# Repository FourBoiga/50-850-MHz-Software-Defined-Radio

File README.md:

# Wideband SDR (50–850 MHz)

## Overview

This project is a custom software-defined radio (SDR) designed to receive signals from approximately **50 MHz to 850 MHz**. The goal is to build a modular, low-cost SDR while learning RF engineering, analog design, FPGA development, and digital signal processing from the ground up.

Unlike many hobby SDRs that rely heavily on highly integrated tuner/transceiver ICs, this design uses discrete RF building blocks for much of the signal chain, including filtering, switching, amplification, mixing, local oscillator generation, and quadrature I/Q conversion.

---

## Goals

* Receive signals from approximately 50 MHz to 850 MHz
* Modular RF front-end
* Good dynamic range
* Low noise figure
* Quadrature I/Q output
* FPGA-based digital signal processing
* USB interface to a host PC
* Eventually interface with SDR software such as SDR++
* Learn professional RF and DSP design techniques

---

## Current Architecture

The signal starts at the antenna and passes through the RF protection and switched bandpass filter bank before being amplified by the LNA. From there it goes through the quadrature receiver and intermediate-frequency conversion stages, producing differential I/Q signals for the ADC. The ADC sends the digitized samples to the FPGA, where the DSP will be performed before the data is eventually sent to the host PC over USB.

---

The receiver uses multiple local oscillator paths generated from PLL frequency synthesizers referenced to a stable TCXO.

---

## Specifications

| Parameter           |                    Specification |
| ------------------- | -------------------------------: |
| Frequency Range     |                      ~50–850 MHz |
| Architecture        | Superheterodyne / Quadrature I/Q |
| Target IF Bandwidth |                           ~1 MHz |
| ADC                 |                       LTC2323-12 |
| ADC Resolution      |                           12-bit |
| ADC Sample Rate     |                   5 MSPS/channel |
| ADC Interface       |                              SPI |
| FPGA                |             Sipeed Tang Nano 20K |
| Controller          |                     STM32 Nucleo |
| Host Interface      |                              USB |
| Output              |              Digital I/Q samples |

These are design targets and specifications; final RF performance will be determined through hardware testing and characterization.

---

## RF Front End

The RF front end consists of:

* RF input protection
* Switched bandpass filter bank
* RF switching
* Low-noise amplifier
* Quadrature receiver/mixer
* Intermediate-frequency conversion
* Local oscillator generation
* PLL frequency synthesizers
* TCXO reference

### Filter Architecture

The original design included additional filtering after the LNA. After reviewing the local RF environment and considering the additional simulation and design time required, the post-LNA filters were removed from the architecture.

The remaining pre-LNA filter bank provides the primary out-of-band filtering before amplification.

---

## Local Oscillator

The local oscillator system uses:

* Stable TCXO reference
* PLL frequency synthesizers
* LO generation for the receiver mixer
* LO generation for the IF mixer

The LO circuitry and synthesizers have been fully integrated into the PCB design.

---

## I/Q Receiver

The receiver produces differential I/Q signals which are digitized by the LTC2323-12 ADC.

During PCB design, the polarity of the Q differential pair was found to be opposite to the polarity expected by the ADC. Rather than rerouting the completed RF section, the differential inputs are intentionally swapped.

This produces a 180° phase inversion of the Q component, which will be corrected digitally in the FPGA by negating the Q samples.

---

## ADC

The SDR uses an **LTC2323-12** dual-channel 12-bit SAR ADC.

The planned configuration uses:

* 12-bit resolution
* 5 MSPS per channel
* Differential I/Q inputs
* SPI interface
* Up to 105 MHz SPI clock

The ADC provides the interface between the analog I/Q receiver and the FPGA's digital signal-processing chain.

---

## FPGA and DSP

The next major development phase is the FPGA firmware and digital signal processing.

The FPGA will initially implement a minimal processing chain capable of receiving and processing the raw I/Q samples from the ADC.

Planned processing includes:

```text
ADC I/Q Samples
       │
       ▼
Digital Filtering
       │
       ▼
Frequency Translation
       │
       ▼
Decimation
       │
       ▼
Sample Formatting
       │
       ▼
USB / Host PC
```

The FPGA development will be done using the **Sipeed Tang Nano 20K**.

The initial goal is not to immediately implement complete SDR++ compatibility. The first fallback target is simply to get raw or minimally processed I/Q samples from the FPGA to a computer.

A simple Python-based host program can then perform FFT processing and display the received spectrum. This provides a straightforward way to verify the complete RF → ADC → FPGA → PC signal path before implementing a more complete SDR software interface.

---

## PCB

The PCB design is now complete and is undergoing a final review before manufacturing.

Completed PCB work includes:

* RF protection
* Bandpass filter bank
* RF switching
* LNA
* Receiver/mixer circuitry
* Local oscillator circuitry
* PLL synthesizers
* I/Q differential routing
* ADC interface
* FPGA interface
* STM32 controller interface
* USB-C circuitry
* Debug SMA connector
* 50 Ω test line
* Test points
* Debug interfaces

The next steps are to perform the final PCB review, finalize the BOM, and submit the project for manufacturing/funding.

---

## Software

### FPGA

Planned FPGA functionality includes:

* LTC2323-12 SPI interface
* I/Q sample capture
* Q polarity correction
* Digital filtering
* Digital frequency translation
* Decimation
* I/Q data formatting
* USB data streaming

### Host PC

The initial host software will likely be a simple Python-based development tool capable of:

* Receiving I/Q samples
* Converting ADC samples into complex I/Q data
* Performing FFTs
* Displaying frequency spectra
* Visualizing received signals

The long-term goal is compatibility with existing SDR software such as SDR++.

---

## Major Engineering Challenges

* Wideband RF filter design
* RF PCB layout
* Maintaining controlled RF impedance
* Mixer integration
* Local oscillator synthesis
* LO phase noise
* Dynamic range
* Noise figure
* I/Q signal integrity
* ADC interfacing
* High-speed SPI
* FPGA DSP implementation
* Fixed-point digital signal processing
* Host-side I/Q streaming
* SDR software integration

One of the primary goals of the project is to understand and implement these individual systems rather than relying on a highly integrated SDR transceiver to hide their operation.

---

## Long-Term Goals

This project is intended to serve as a platform for experimentation and learning in:

* RF Engineering
* Analog Electronics
* RF PCB Design
* FPGA Development
* Digital Signal Processing
* Software-Defined Radio
* Communication Systems

Future revisions may improve filtering, dynamic range, instantaneous bandwidth, frequency coverage, DSP capabilities, and host software.

---

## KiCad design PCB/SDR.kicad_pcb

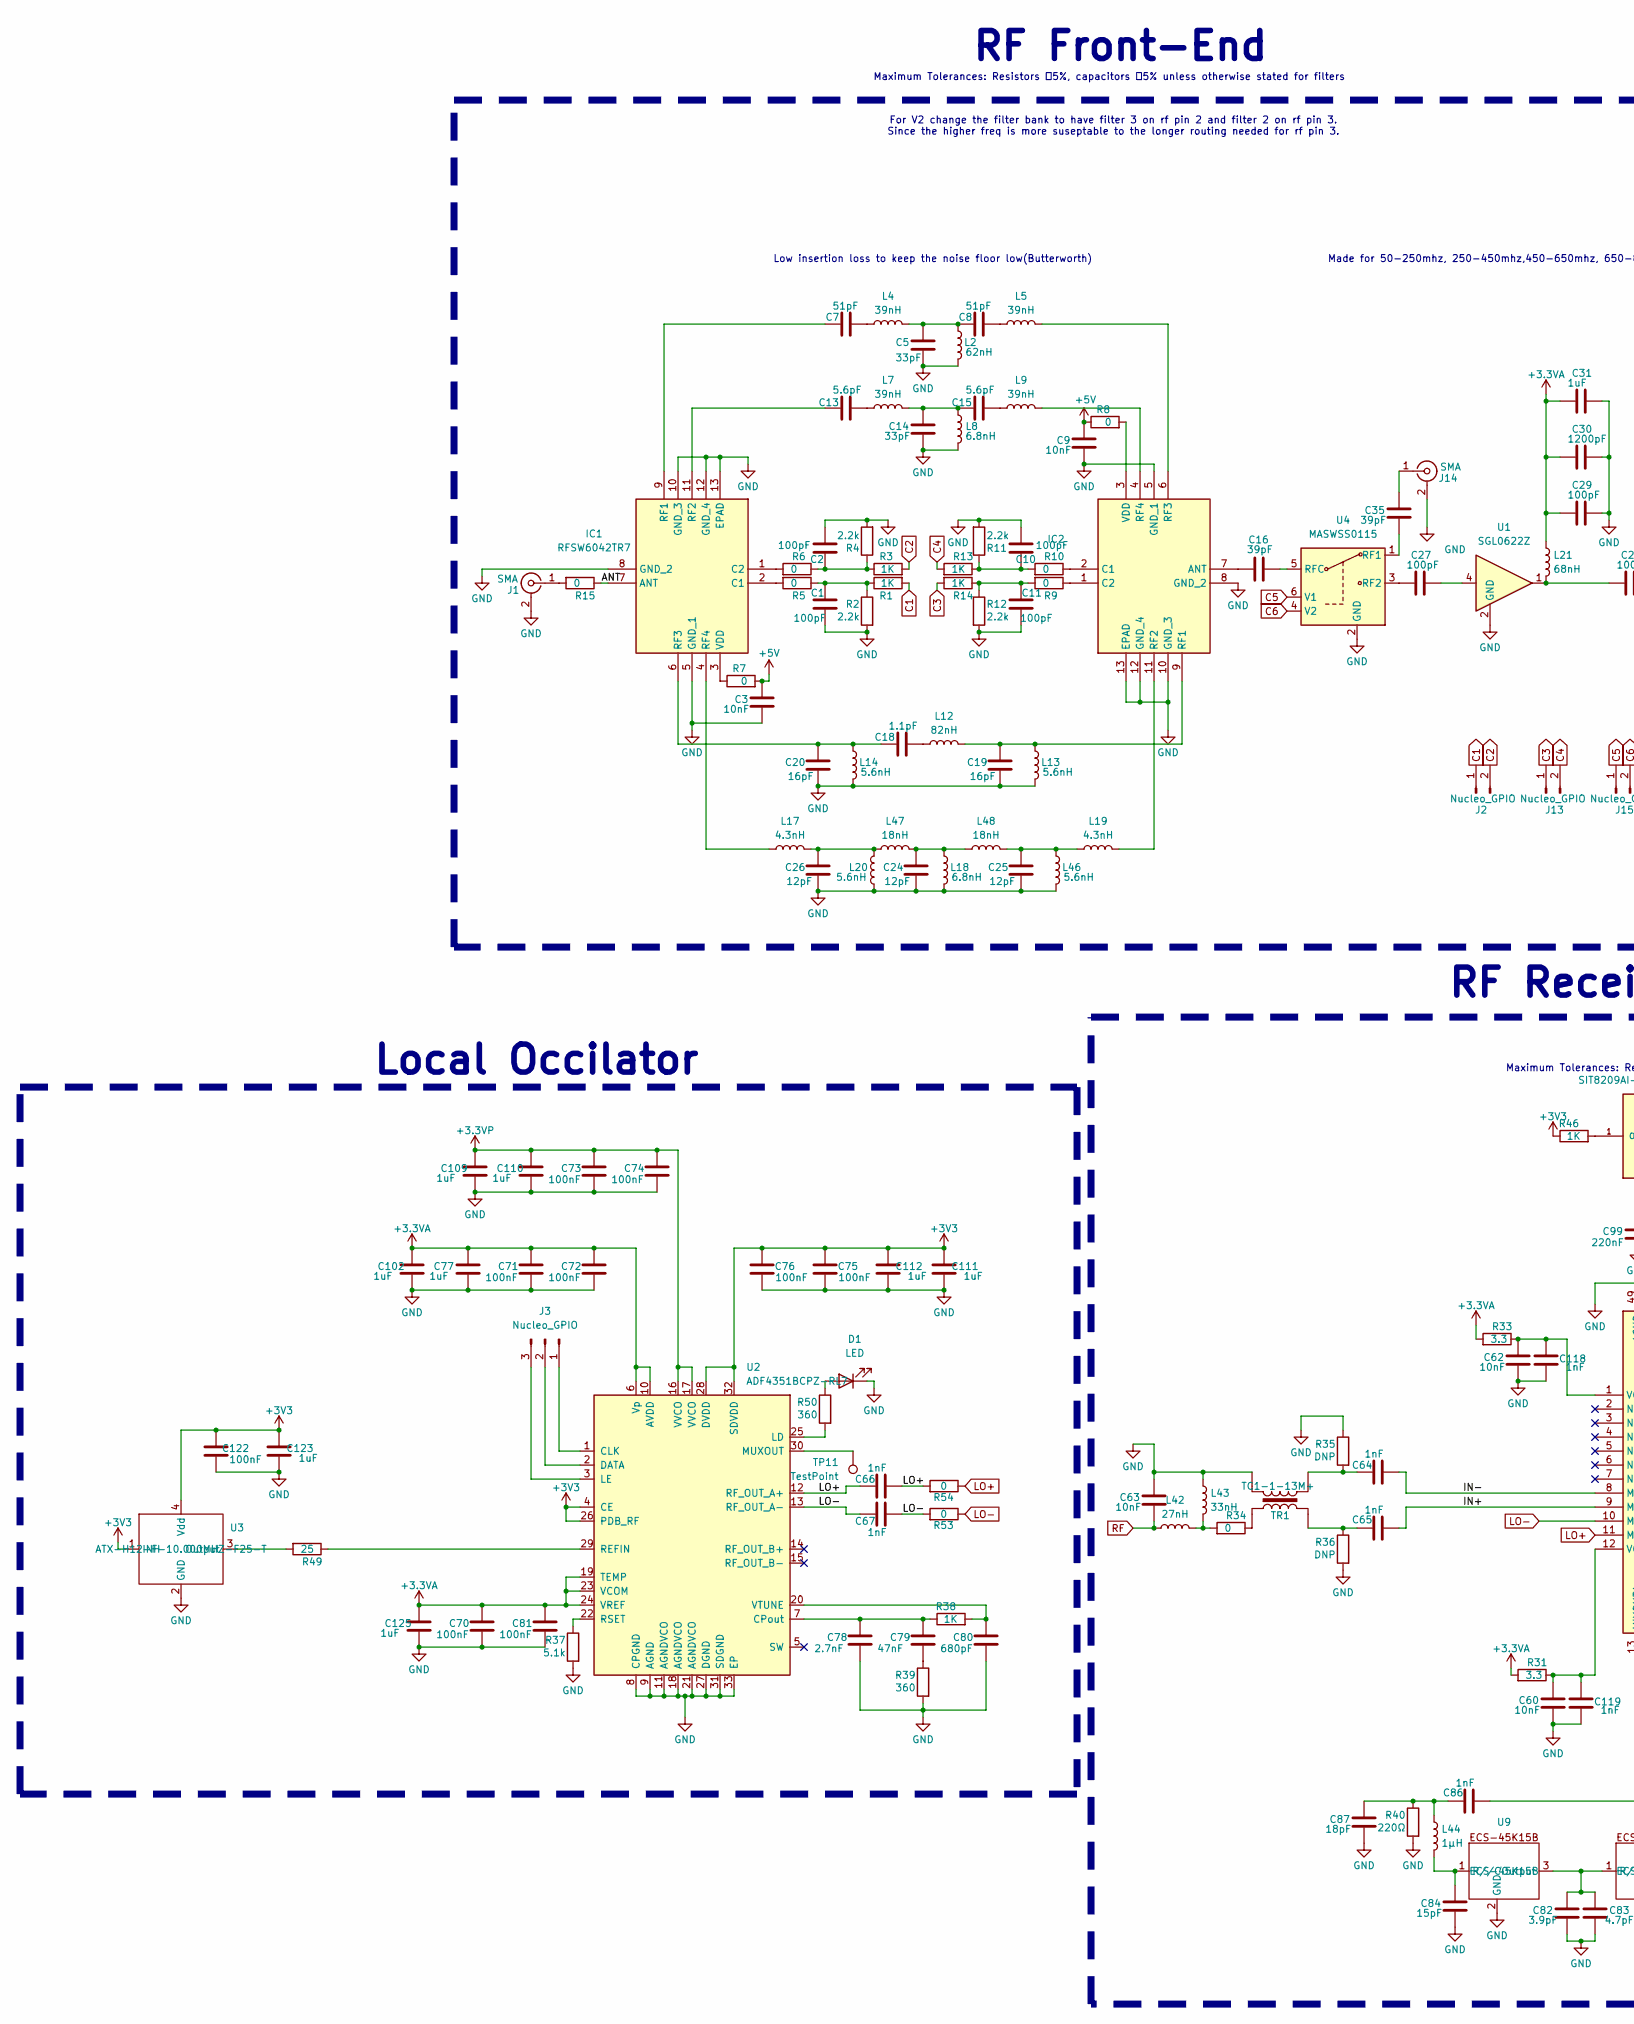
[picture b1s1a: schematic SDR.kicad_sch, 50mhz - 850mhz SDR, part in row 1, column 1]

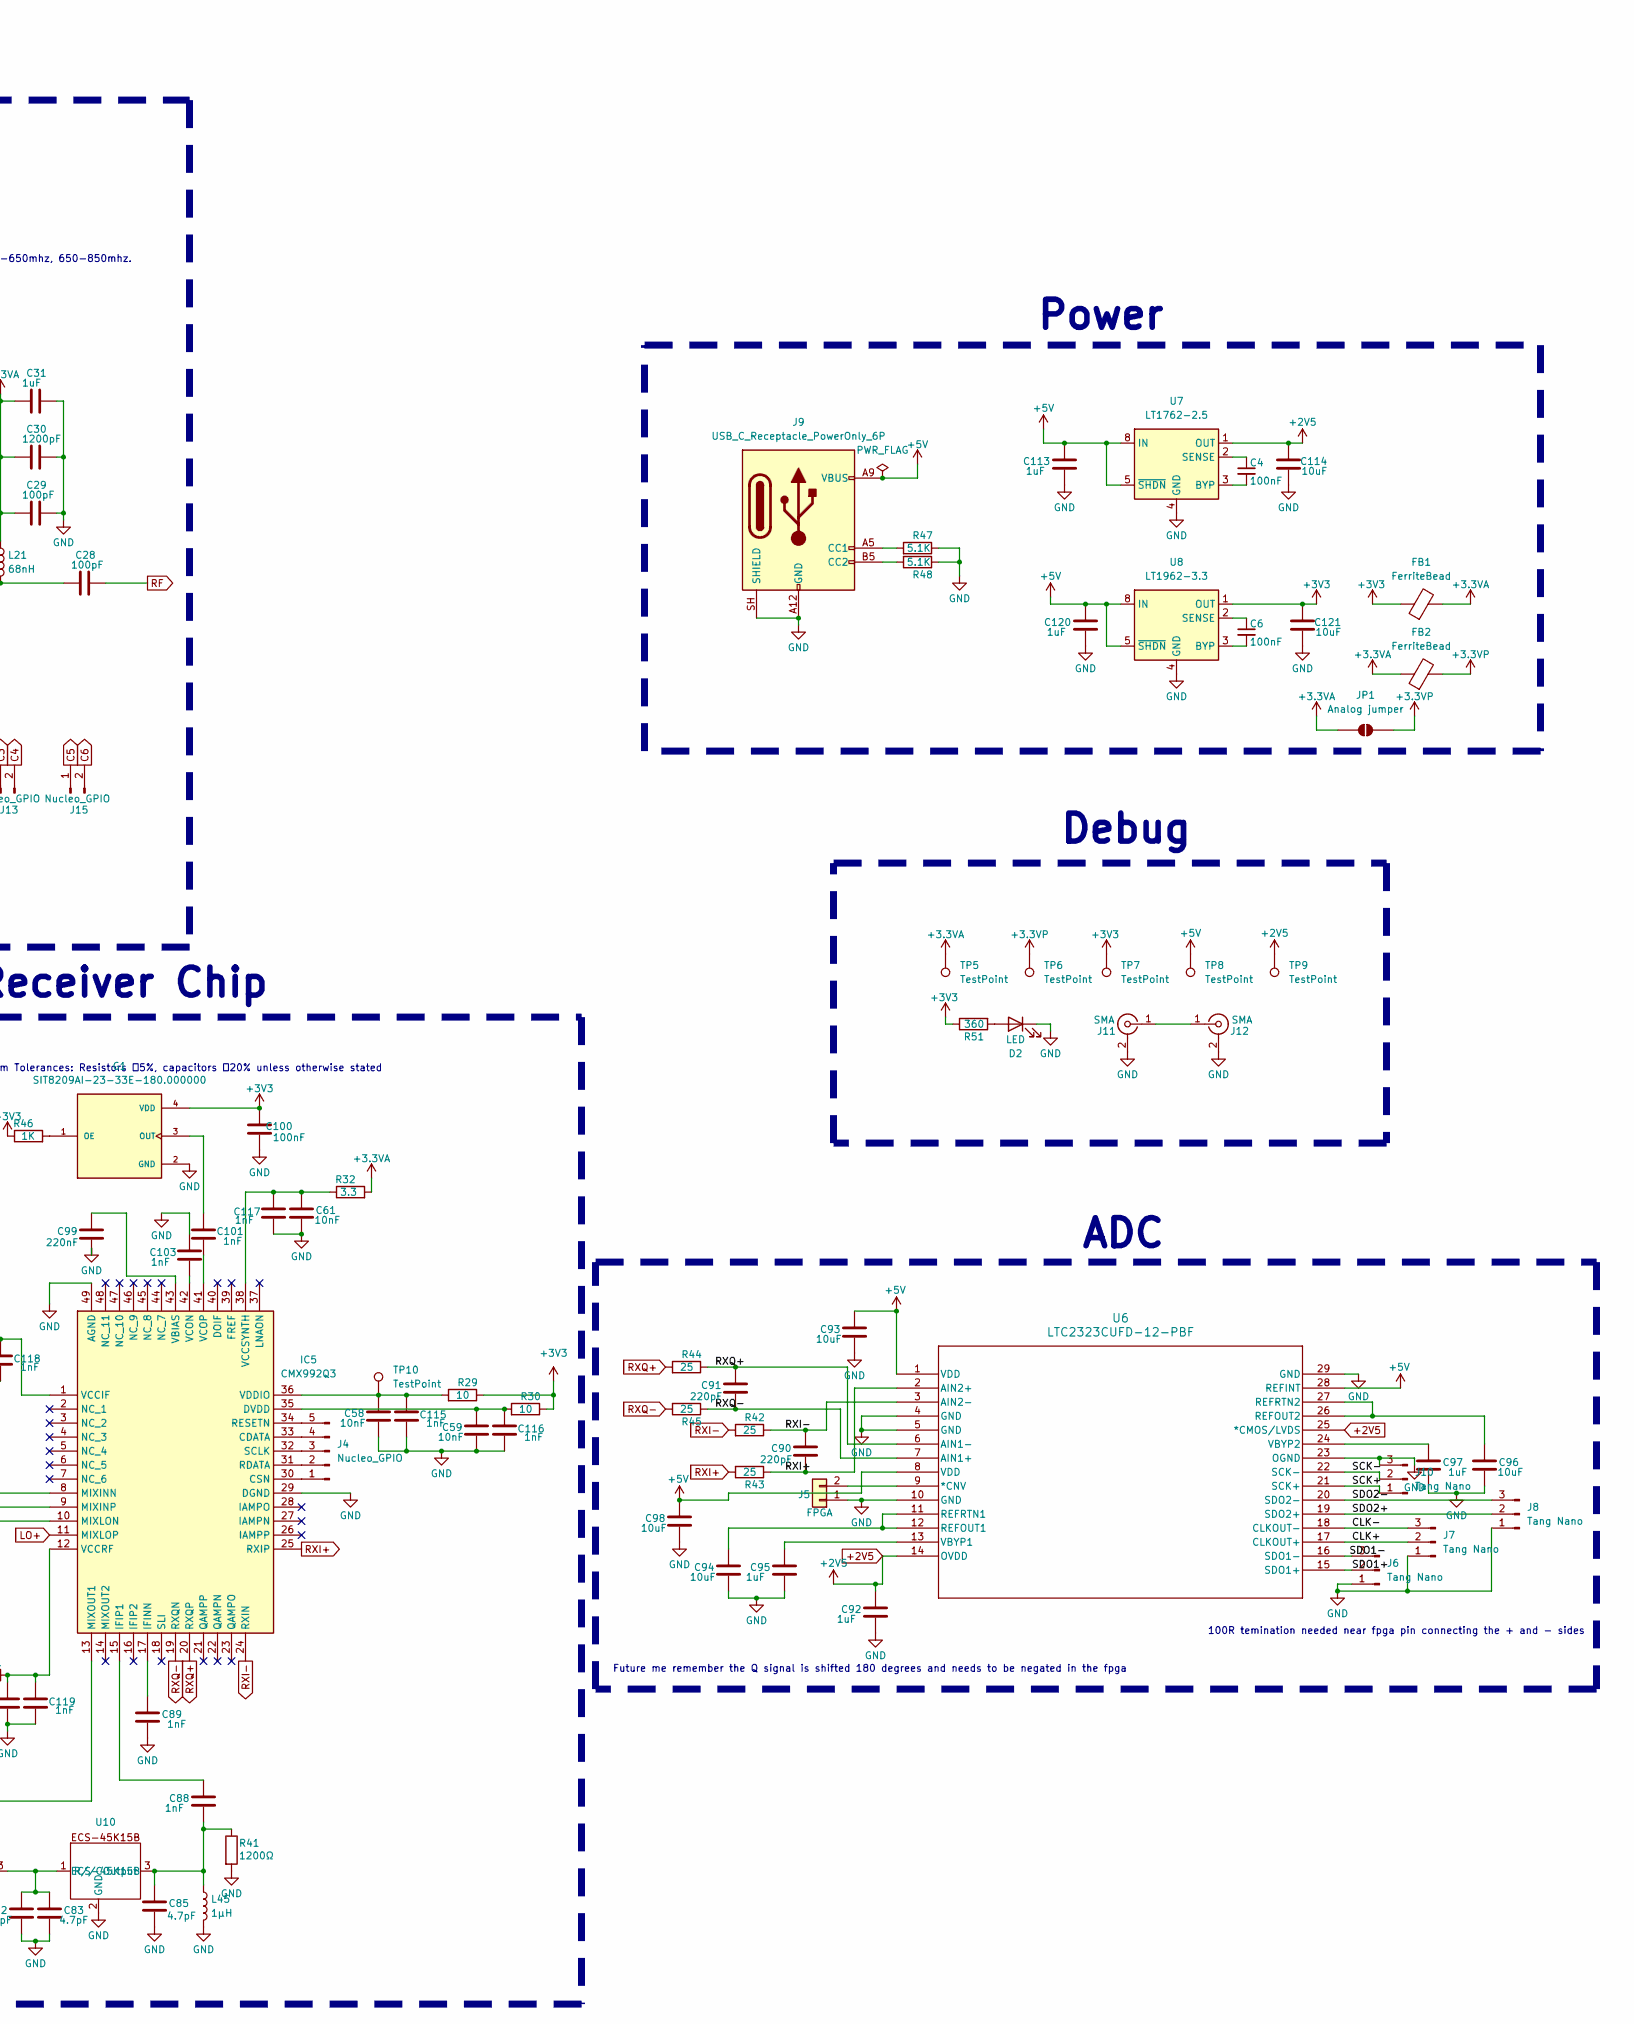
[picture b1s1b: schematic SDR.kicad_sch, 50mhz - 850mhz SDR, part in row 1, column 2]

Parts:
C1, C2, C10, C11, C27, C28, C29: 100pF; C_0402_1005Metric
C3, C9, C58, C59, C60, C61, C62, C63: 10nF; C_0805_2012Metric
C4, C6, C70, C73, C74, C75, C76, C81, C100: 100nF; C_0603_1608Metric
C5, C14: 33pF; C_0402_1005Metric
C7, C8: 51pF; C_0402_1005Metric
C13, C15: 5.6pF; C_0402_1005Metric
C16, C35: 39pF; C_0402_1005Metric
C18: 1.1pF; C_0402_1005Metric
C19, C20: 16pF; C_0402_1005Metric
C24, C25, C26: 12pF; C_0402_1005Metric
C30: 1200pF; C_0402_1005Metric
C31, C77, C92, C95, C97, C102, C109, C110, C111, C112, C113, C120, C123, C125: 1uF; C_0603_1608Metric
C64, C65, C66, C67, C86, C88, C89, C101, C103, C115, C116, C117, C118, C119: 1nF; C_0603_1608Metric
C71, C72, C122: 100nF; C_0402_1005Metric
C78: 2.7nF; C_0603_1608Metric
C79: 47nF; C_0603_1608Metric
C80: 680pF; C_0603_1608Metric
C82: 3.9pF; C_0603_1608Metric
C83, C85: 4.7pF; C_0603_1608Metric
C84: 15pF; C_0603_1608Metric
C87: 18pF; C_0603_1608Metric
C90, C91: 220pF; C_0603_1608Metric
C93, C94, C96, C98: 10uF; C_0805_2012Metric
C99: 220nF; C_0603_1608Metric
C114, C121: 10uF; C_0603_1608Metric
D1, D2: LED; LED_0603_1608Metric
FB1, FB2: FerriteBead; L_0603_1608Metric
G1: SIT8209AI-23-33E-180.000000; OSC_SiT8209AI-32-25E-133.300000; PARTREV 1.1
IC1, IC2: RFSW6042TR7; QFN40P180X180X60-13N-D; Mouser Part Number 772-RFSW6042
IC5: CMX992Q3; QFN50P700X700X100-49N-D; Mouser Part Number 226-CMX992Q3
J1, J11, J12: SMA; SMA_Amphenol_132289_EdgeMount
J2, J13, J15: Nucleo_GPIO; PinHeader_1x02_P1.00mm_Vertical
J3: Nucleo_GPIO; PinHeader_1x03_P1.00mm_Vertical
J4: Nucleo_GPIO; PinHeader_1x05_P1.00mm_Vertical
J5: FPGA; SolderWire-0.25sqmm_1x02_P4.2mm_D0.65mm_OD1.7mm
J6, J7, J8, J10: Tang Nano; SolderWire-0.25sqmm_1x03_P4.5mm_D0.65mm_OD2mm
J9: USB_C_Receptacle_PowerOnly_6P; USB_C_Receptacle_GCT_USB4125-xx-x-0190_6P_TopMnt_Horizontal
J14: SMA; SMA_Amphenol_132291-12_Vertical
JP1: Analog jumper; SolderJumper-2_P1.3mm_Open_Pad1.0x1.5mm
L2: 62nH; L_0603_1608Metric
L4, L5, L7, L9: 39nH; L_0603_1608Metric
L8, L18: 6.8nH; L_0603_1608Metric
L12: 82nH; L_0805_2012Metric
L13, L14, L20, L46: 5.6nH; L_0402_1005Metric
L17, L19: 4.3nH; L_0402_1005Metric
L21: 68nH; L_0603_1608Metric
L42: 27nH; L_0603_1608Metric
L43: 33nH; L_0603_1608Metric
L44, L45: 1μH; L_0805_2012Metric
L47, L48: 18nH; L_0603_1608Metric
R1, R3, R13, R14, R38, R46: 1K; R_0402_1005Metric
R2, R4, R11, R12: 2.2k; R_0402_1005Metric
R5, R6, R7, R8, R9, R10, R15: 0; R_0402_1005Metric
R29, R30: 10; R_0402_1005Metric
R31, R32, R33: 3.3; R_0603_1608Metric
R34, R53, R54: 0; R_0603_1608Metric
R35, R36: DNP; R_0603_1608Metric
R37: 5.1k; R_0402_1005Metric
R39, R51: 360; R_0603_1608Metric
R40: 220Ω; R_0603_1608Metric
R41: 1200Ω; R_0603_1608Metric
R42, R43, R44, R45, R49: 25; R_0805_2012Metric
R47, R48: 5.1K; R_0402_1005Metric
R50: 360; R_0402_1005Metric
TP5, TP6, TP7, TP8, TP9: TestPoint; TestPoint_Pad_D4.0mm
TP10, TP11: TestPoint; TestPoint_Pad_D2.0mm
TR1: TC1-1-13M+; AT224-1A
U1: SGL0622Z; DFN-8-1EP_2x2mm_P0.5mm_EP0.6x1.2mm
U2: ADF4351BCPZ-RL7; LFCSP-32-1EP_5x5mm_P0.5mm_EP3.25x3.25mm
U3: ATX-H12-F-10.000MHZ-F25-T; ATXH12F10000MHzF25T
U4: MASWSS0115; SOT-363_SC-70-6
U6: LTC2323CUFD-12-PBF; QFN-28_UFD_LIT
U7: LT1762-2.5; MSOP-8_3x3mm_P0.65mm
U8: LT1962-3.3; MSOP-8_3x3mm_P0.65mm
U9, U10: ECS-45K15B; Untitled

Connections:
+2V5: C92.1, C114.1, TP9.1 (1_1), U6.14 (OVDD), U6.25 (*CMOS/LVDS), U7.1 (OUT)
+3.3VA: C29.2, C30.2, C31.2, C70.1, C71.1, C72.1, C77.1, C81.1, C102.1, C125.1, FB1.2, FB2.1, JP1.1 (A), L21.1, R31.2, R32.2, R33.2, TP5.1 (1_1), U2.6 (Vp), U2.10 (AVDD), U2.19 (TEMP), U2.23 (VCOM), U2.24 (VREF)
+3.3VP: C73.1, C74.1, C109.1, C110.1, FB2.2, JP1.2 (B), TP6.1 (1_1), U2.16 (VVCO), U2.17 (VVCO)
+3V3: C75.1, C76.1, C100.1, C111.1, C112.1, C121.1, C122.1, C123.1, FB1.1, G1.4 (VDD), R29.1, R30.1, R46.1, R51.1, TP7.1 (1_1), U2.4 (CE), U2.26 (PDB_RF), U2.28 (DVDD), U2.32 (SDVDD), U3.1 (INH), U3.4 (Vdd), U8.1 (OUT)
+5V: C3.1, C9.1, C93.1, C98.1, C113.1, C120.1, J9.A9 (VBUS), J9.B9 (VBUS), R7.2, R8.1, TP8.1 (1_1), U6.1 (VDD), U6.8 (VDD), U6.28 (REFINT), U7.5 (~SHDN), U7.8 (IN), U8.5 (~SHDN), U8.8 (IN)
/ANT: IC1.7 (ANT), R15.1
/CLK+: J7.2, U6.17 (CLKOUT+)
/CLK-: J7.3, U6.18 (CLKOUT-)
/IN+: C65.1, IC5.9 (MIXINP)
/IN-: C64.1, IC5.8 (MIXINN)
/SCK+: J10.1, U6.21 (SCK+)
/SCK-: J10.2, U6.22 (SCK-)
/SDO1+: J6.2, U6.15 (SDO1+)
/SDO1-: J6.3, U6.16 (SDO1-)
/SDO2+: J8.2, U6.19 (SDO2+)
/SDO2-: J8.3, U6.20 (SDO2-)
C1: J2.1, R1.2
C2: J2.2, R3.2
C3: J13.1, R14.2
C4: J13.2, R13.2
C5: J15.1, U4.6 (V1)
C6: J15.2, U4.4 (V2)
GND: C1.2, C2.2, C3.2, C5.2, C9.2, C10.2, C11.2, C14.2, C19.2, C20.2, C24.2, C25.2, C26.2, C29.1, C30.1, C31.1, C58.2, C59.2, C60.2, C61.2, C62.2, C63.1, C70.2, C71.2, C72.2, C73.2, C74.2, C75.2, C76.2, C77.2, C78.2, C80.2, C81.2, C82.2, C83.2, C84.2, C85.2, C87.2, C89.2, C92.2, C93.2, C94.2, C95.2, C96.2, C97.2, C98.2, C99.2, C100.2, C102.2, C103.1, C109.2, C110.2, C111.2, C112.2, C113.2, C114.2, C115.2, C116.2, C117.2, C118.2, C119.2, C120.2, C121.2, C122.2, C123.2, C125.2, D1.1 (K), D2.1 (K), G1.2 (GND), IC1.5 (GND_1), IC1.8 (GND_2), IC1.10 (GND_3), IC1.12 (GND_4), IC1.13 (EPAD), IC2.5 (GND_1), IC2.8 (GND_2), IC2.10 (GND_3), IC2.12 (GND_4), IC2.13 (EPAD), IC5.29 (DGND), IC5.49 (AGND), J1.2 (Ext), J5.1, J6.1, J7.1, J8.1, J9.A12 (GND), J9.B12 (GND), J9.SH (SHIELD), J10.3, J11.2 (Ext), J12.2 (Ext), J14.2 (Ext), L2.2, L8.2, L13.2, L14.2, L18.2, L20.2, L43.1, L45.2, L46.2, R2.2, R4.2, R11.2, R12.2, R35.1, R36.2, R37.2, R39.2, R40.2, R41.2, R47.1, R48.1, TR1.6, U1.2 (GND), U1.3 (GND), U1.5 (GND), U1.6 (GND), U1.7 (GND), U1.8 (GND), U1.9 (GND), U2.8 (CPGND), U2.9 (AGND), U2.11 (AGNDVCO), U2.18 (AGNDVCO), U2.21 (AGNDVCO), U2.27 (DGND), U2.31 (SDGND), U2.33 (EP), U3.2 (GND), U4.2 (GND), U6.4 (GND), U6.5 (GND), U6.10 (GND), U6.23 (OGND), U6.29 (GND), U7.4 (GND), U8.4 (GND), U9.2 (GND), U10.2 (GND)
LO+: C66.1, C66.2, IC5.11 (MIXLOP), R54.1, R54.2, U2.12 (RF_OUT_A+)
LO-: C67.1, C67.2, IC5.10 (MIXLON), R53.1, R53.2, U2.13 (RF_OUT_A-)
unnamed: C1.1, R1.1, R2.1, R5.1
unnamed: C2.1, R3.1, R4.1, R6.1
unnamed: C5.1, C8.2, L2.1, L4.2
unnamed: C7.1, L4.1
unnamed: C8.1, L5.1
unnamed: C10.1, R10.2, R11.1, R13.1
unnamed: C11.1, R9.2, R12.1, R14.1
unnamed: C13.1, L7.1
unnamed: C14.1, C15.2, L7.2, L8.1
unnamed: C15.1, L9.1
unnamed: C18.1, L12.1
unnamed: C24.1, L18.1, L47.2, L48.1
unnamed: C25.1, L19.1, L46.1, L48.2
unnamed: C26.1, L17.2, L20.1, L47.1
unnamed: C27.1, U1.4
unnamed: C28.2, L21.2, U1.1
unnamed: C64.2, R35.2, TR1.1
unnamed: C65.2, R36.1, TR1.3
unnamed: C79.2, R39.1
unnamed: C86.2, C87.1, L44.1, R40.1
unnamed: D1.2 (A), R50.1
unnamed: D2.2 (A), R51.2
unnamed: G1.1 (OE), R46.2
unnamed: C101.1, G1.3 (OUT)
unnamed: IC1.2 (C1), R5.2
unnamed: IC1.1 (C2), R6.2
unnamed: C7.2, IC1.9 (RF1)
unnamed: C13.2, IC1.11 (RF2)
unnamed: C18.2, C20.1, IC1.6 (RF3), L14.1
unnamed: IC1.4 (RF4), L17.1
unnamed: IC1.3 (VDD), R7.1
unnamed: C16.2, IC2.7 (ANT)
unnamed: IC2.2 (C1), R10.1
unnamed: IC2.1 (C2), R9.1
unnamed: C19.1, IC2.9 (RF1), L12.2, L13.1
unnamed: IC2.11 (RF2), L19.2
unnamed: IC2.6 (RF3), L5.2
unnamed: IC2.4 (RF4), L9.2
unnamed: IC2.3 (VDD), R8.2
unnamed: IC5.33 (CDATA), J4.4
unnamed: IC5.30 (CSN), J4.1
unnamed: C59.1, C116.1, IC5.35 (DVDD), R30.2
unnamed: C89.1, IC5.17 (IFINN)
unnamed: C88.1, IC5.15 (IFIP1)
unnamed: C86.1, IC5.13 (MIXOUT1)
unnamed: IC5.31 (RDATA), J4.2
unnamed: IC5.34 (RESETN), J4.5
unnamed: IC5.32 (SCLK), J4.3
unnamed: C99.1, IC5.43 (VBIAS)
unnamed: C62.1, C118.1, IC5.1 (VCCIF), R33.1
unnamed: C60.1, C119.1, IC5.12 (VCCRF), R31.1
unnamed: C61.1, C117.1, IC5.38 (VCCSYNTH), R32.1
unnamed: C103.2, IC5.42 (VCON)
unnamed: C101.2, IC5.41 (VCOP)
unnamed: C58.1, C115.1, IC5.36 (VDDIO), R29.2, TP10.1 (1_1)
unnamed: J1.1 (In), R15.2
unnamed: J3.1, U2.1 (CLK)
unnamed: J3.2, U2.2 (DATA)
unnamed: J3.3, U2.3 (LE)
unnamed: J5.2, U6.9 (*CNV)
unnamed: J9.A5 (CC1), R47.2
unnamed: J9.B5 (CC2), R48.2
unnamed: J11.1 (In), J12.1 (In)
unnamed: C35.1, J14.1 (In)
unnamed: L42.2, L43.2, R34.2
unnamed: R34.1, TR1.4
unnamed: C78.1, C79.1, R38.1, U2.7 (CPout)
unnamed: R50.2, U2.25 (LD)
unnamed: TP11.1 (1_1), U2.30 (MUXOUT)
unnamed: R49.1, U2.29 (REFIN)
unnamed: R37.1, U2.22 (RSET)
unnamed: C80.1, R38.2, U2.20 (VTUNE)
unnamed: R49.2, U3.3 (Output)
unnamed: C35.2, U4.1 (RF1)
unnamed: C27.2, U4.3 (RF2)
unnamed: C16.1, U4.5 (RFC)
unnamed: C94.1, U6.11 (REFRTN1), U6.12 (REFOUT1)
unnamed: C96.1, U6.26 (REFOUT2), U6.27 (REFRTN2)
unnamed: C95.1, U6.13 (VBYP1)
unnamed: C97.1, U6.24 (VBYP2)
unnamed: C4.2, U7.3 (BYP)
unnamed: C4.1, U7.2 (SENSE)
unnamed: C6.2, U8.3 (BYP)
unnamed: C6.1, U8.2 (SENSE)
unnamed: C84.1, L44.2, U9.1 (R//C)
unnamed: C85.1, C88.2, L45.1, R41.1, U10.3 (Output)
unnamed: C82.1, C83.1, U9.3 (Output), U10.1 (R//C)
RF: C28.1, C63.2, L42.1
RXI+: C90.2, IC5.25 (RXIP), R43.1, R43.2, U6.2 (AIN2+)
RXI-: C90.1, IC5.24 (RXIN), R42.1, R42.2, U6.3 (AIN2-)
RXQ+: C91.1, IC5.20 (RXQP), R44.1, R44.2, U6.6 (AIN1-)
RXQ-: C91.2, IC5.19 (RXQN), R45.1, R45.2, U6.7 (AIN1+)

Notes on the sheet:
100R temination needed near fpga pin connecting the + and - sides
Future me remember the Q signal is shifted 180 degrees and needs to be negated in the fpga
Low insertion loss to keep the noise floor low(Butterworth)
RF Front-End
Debug
Maximum Tolerances: Resistors 5%, capacitors 5% unless otherwise stated for filters
For V2 change the filter bank to have filter 3 on rf pin 2 and filter 2 on rf pin 3. Since the higher freq is more suseptable to the longer routing needed for rf pin 3.
Maximum Tolerances: Resistors 5%, capacitors 20% unless otherwise stated
Power
Made for 50-250mhz, 250-450mhz,450-650mhz, 650-850mhz.
ADC
Local Occilator
RF Receiver Chip

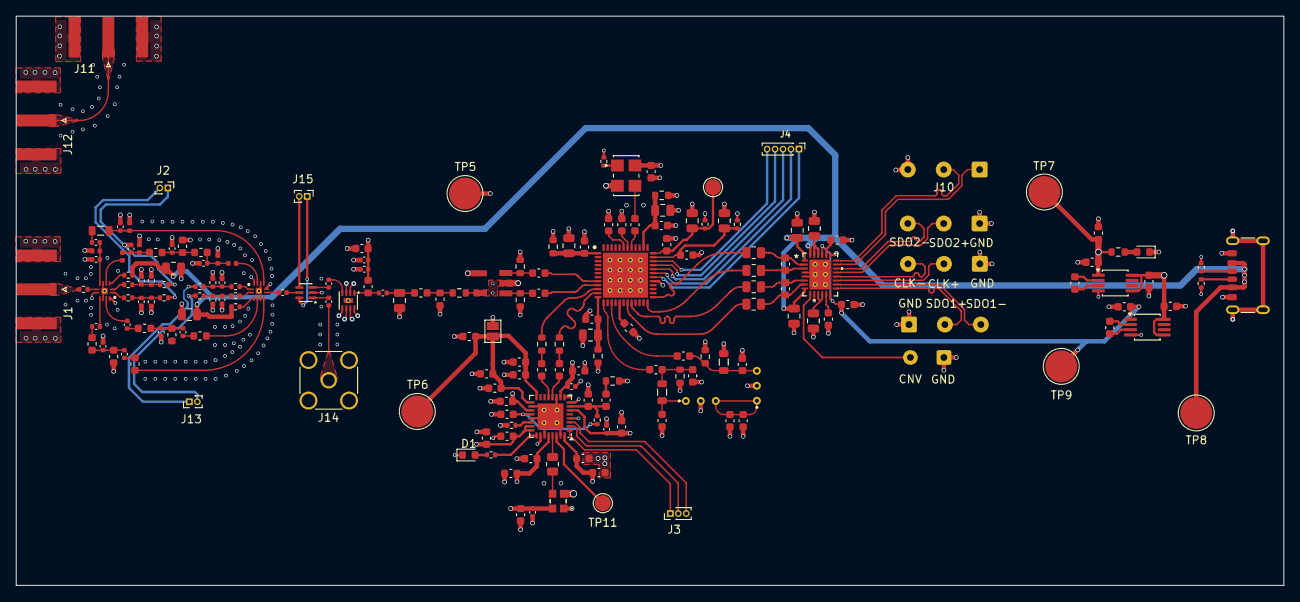
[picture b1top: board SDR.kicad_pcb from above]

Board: 4 copper layers, 158.8 x 71.3 mm, 189 parts (0 on the bottom side), 117 nets.
